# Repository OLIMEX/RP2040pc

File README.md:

# RP2040pc
All in one computer with 4 USB hosts, Stereo Audio, HDMI output. Supports USB Flash drives, USB keyboards, USB Gamepads.

https://www.olimex.com/Products/RaspberryPi/RP2040pc/

## Licensee
* Hardware is released under CERN Open Hardware Licence Version 2 - Strongly Reciprocal
* Software is released under MIT Licensee
* Documentation is released under CC BY-SA 4.0

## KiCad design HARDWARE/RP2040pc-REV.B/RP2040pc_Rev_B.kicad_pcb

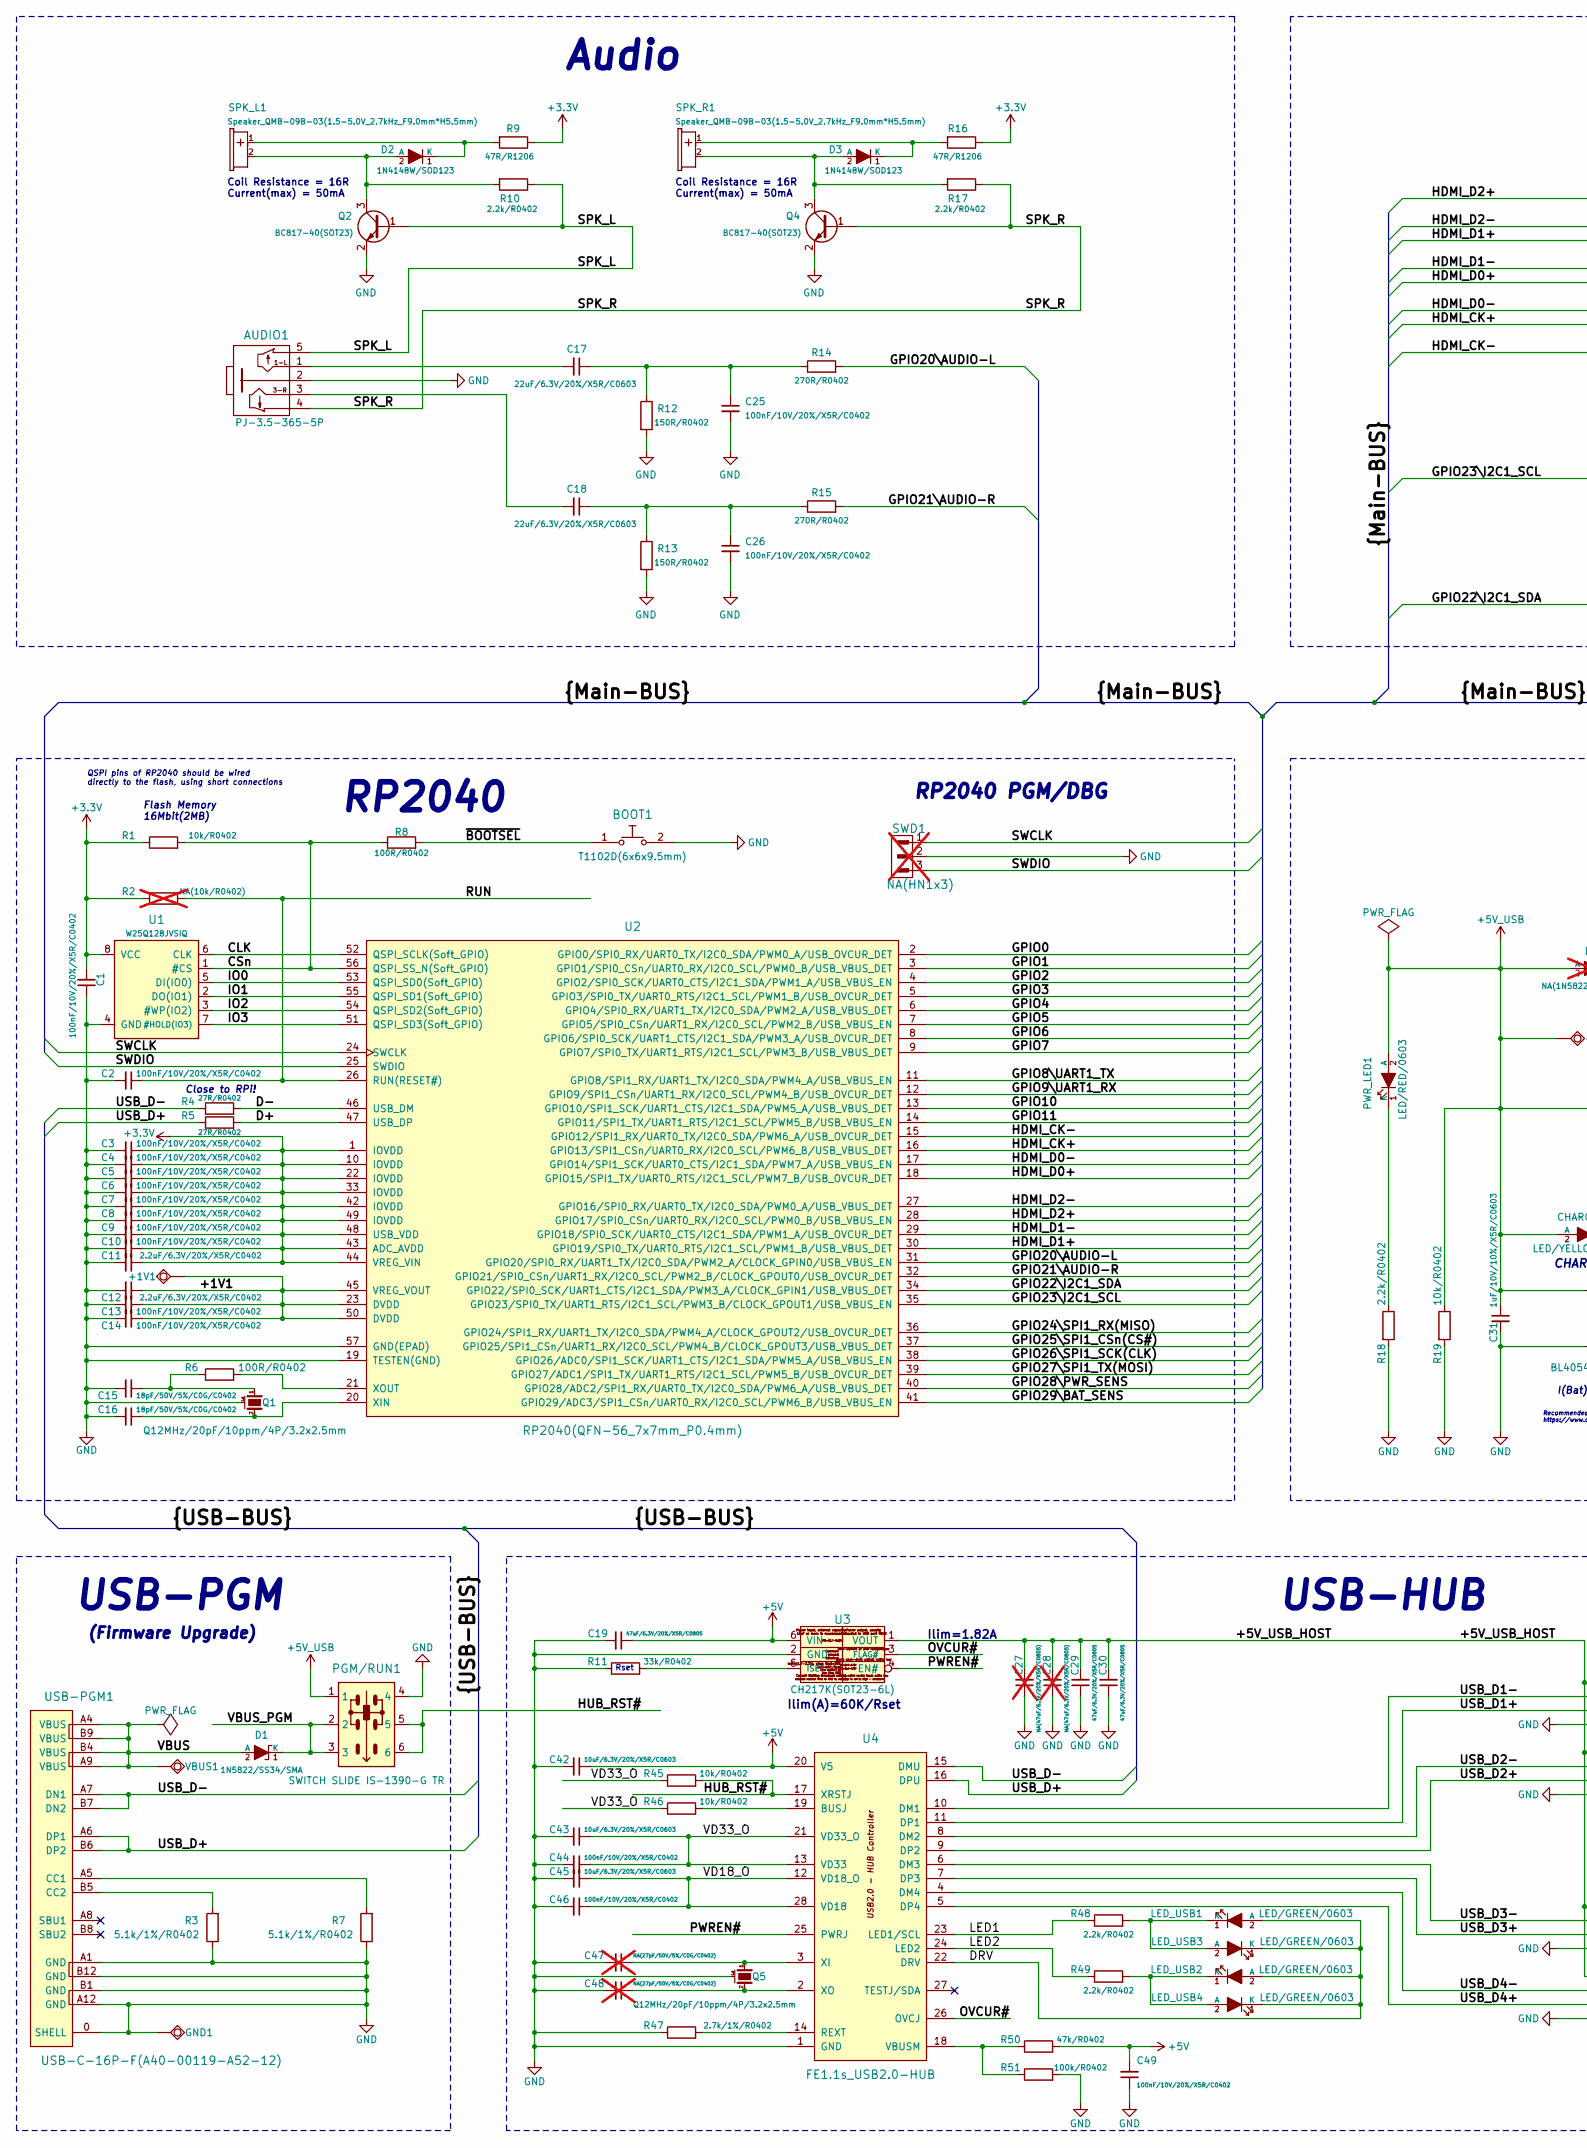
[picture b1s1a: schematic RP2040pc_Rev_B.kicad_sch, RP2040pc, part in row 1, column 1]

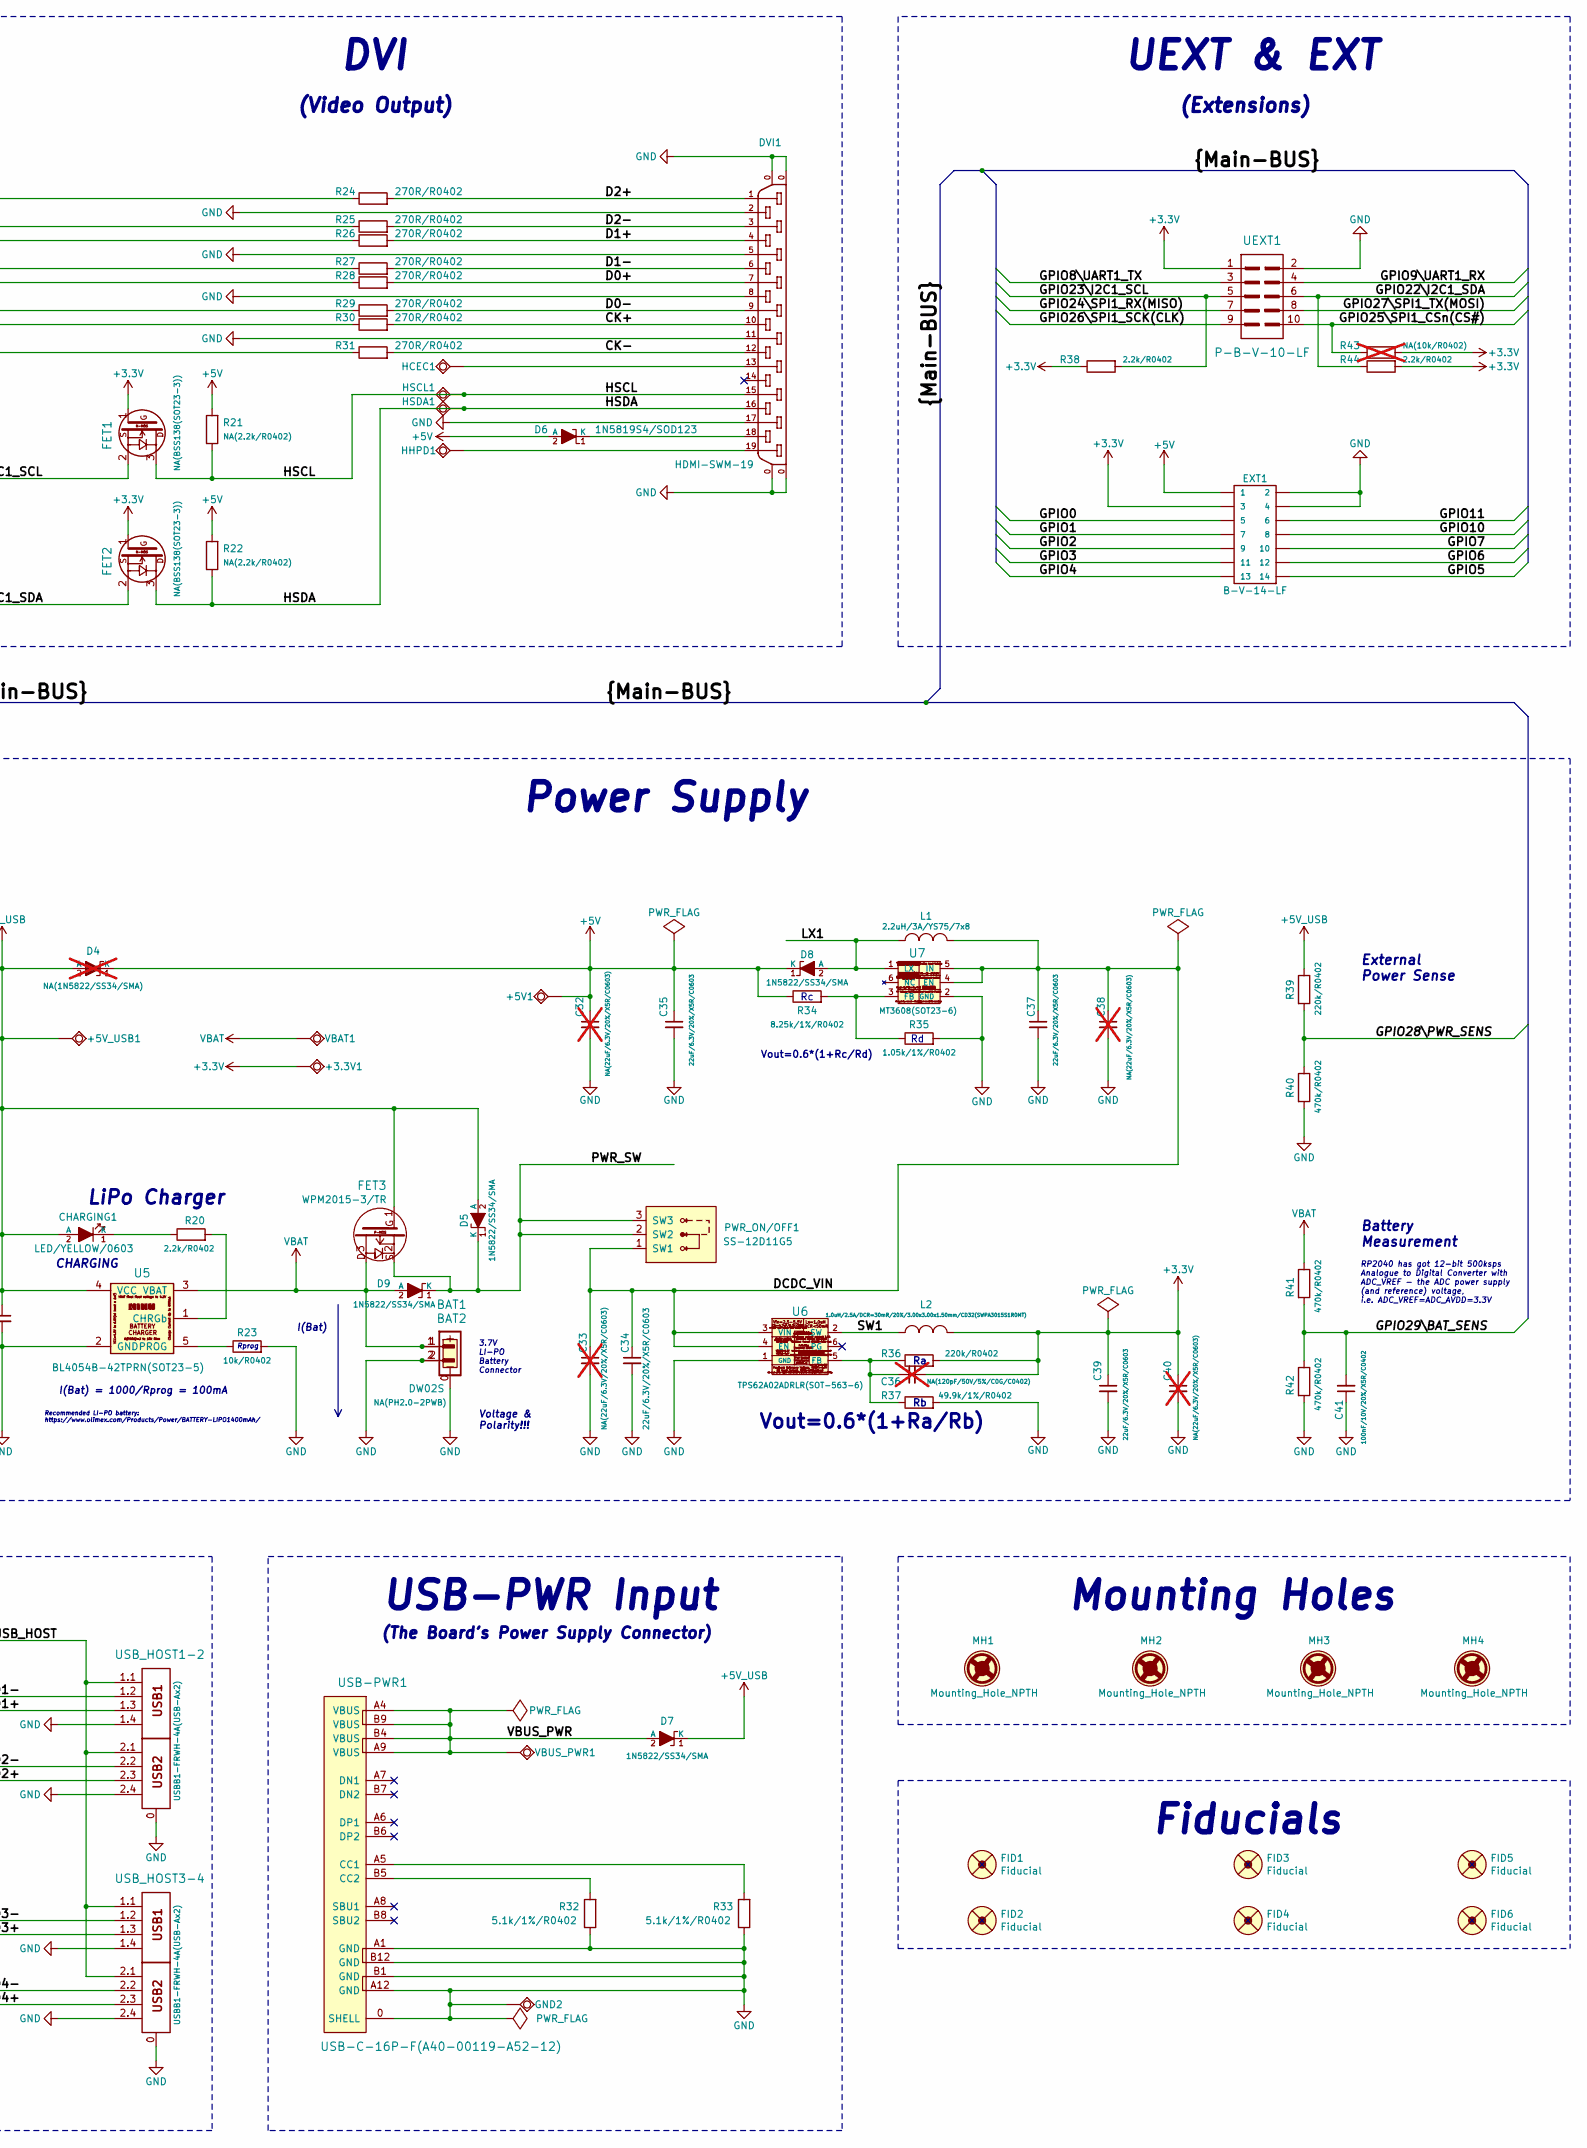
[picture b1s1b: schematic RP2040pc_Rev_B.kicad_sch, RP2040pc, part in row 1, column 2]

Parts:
+1V1, +3.3V1, +5V1, +5V_USB1: TESTPAD; TESTPAD_40-ROUND
AUDIO1: PJ-3.5-365-5P; SCJ325P00XG0B02G
BAT1: DW02S; LIPO_BAT_VERTICAL_DW02S
BAT2: NA(PH2.0-2PWB); PH2.0-2PWB
BOOT1: T1102D(6x6x9.5mm); T1102D_6x6
C1, C2, C3, C4, C5, C6, C7, C8, C9, C10, C13, C14, C25, C26, C41, C44, C46, C49: 100nF/10V/20%/X5R/C0402; C_0402_5MIL_DWS
C11, C12: 2.2uF/6.3V/20%/X5R/C0402; C_0402_5MIL_DWS
C15, C16: 18pF/50V/5%/C0G/C0402; C_0402_5MIL_DWS
C17, C18, C34, C35, C37, C39: 22uF/6.3V/20%/X5R/C0603; C_0603_5MIL_DWS
C19, C29, C30: 47uF/6.3V/20%/X5R/C0805; C_0805_5MIL_DWS
C27, C28: NA(47uF/6.3V/20%/X5R/C0805); C_0805_5MIL_DWS; not fitted
C31: 1uF/10V/10%/X5R/C0603; C_0603_5MIL_DWS
C32, C33, C38, C40: NA(22uF/6.3V/20%/X5R/C0603); C_0603_5MIL_DWS; not fitted
C36: NA(120pF/50V/5%/C0G/C0402); C_0402_5MIL_DWS; not fitted
C42, C43, C45: 10uF/6.3V/20%/X5R/C0603; C_0603_5MIL_DWS
C47, C48: NA(27pF/50V/5%/C0G/C0402); C_0402_5MIL_DWS; not fitted
CHARGING1: LED/YELLOW/0603; LED_0603_KA
D1, D5, D7, D8, D9: 1N5822/SS34/SMA; SMA-KA
D2, D3: 1N4148W/SOD123; SOD-123_1C-2A_KA
D4: NA(1N5822/SS34/SMA); SMA-KA; not fitted
D6: 1N5819S4/SOD123; SOD-123_1C-2A_KA
DVI1: HDMI-SWM-19; HDMI-SWM-19_Paste
EXT1: B-V-14-LF; GBH-254-SMT-14
FET1, FET2: NA(BSS138(SOT23-3)); SOT23
FET3: WPM2015-3/TR; SOT23
FID1, FID2, FID3: Fiducial; Fiducial1x3_Paste
FID4, FID5, FID6: Fiducial; Fiducial1x3
GND1: TESTPAD; TEST_PAD40x70_SQUARE
GND2: TESTPAD; TESTPAD_40-ROUND
HCEC1: TESTPAD; TESTPAD_40-ROUND
HHPD1: TESTPAD; TESTPAD_40-ROUND
HSCL1: TESTPAD; TESTPAD_40-ROUND
HSDA1: TESTPAD; TESTPAD_40-ROUND
L1: 2.2uH/3A/YS75/7x8; YS75_7X8MM
L2: 1.0uH/2.5A/DCR=30mR/20%/3.00x3.00x1.50mm/CD32(SWP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; CD32
LED_USB1, LED_USB2, LED_USB3, LED_USB4: LED/GREEN/0603; LED_0603_KA
MH1, MH2, MH3, MH4: Mounting_Hole_NPTH; Mounting_Hole_Drill-3.3mm_Clerance-7mm
PGM/RUN1: SWITCH SLIDE IS-1390-G TR; SWITCH_SLIDE_IS-1390-G_TR
PWR_LED1: LED/RED/0603; LED_0603_KA
PWR_ON/OFF1: SS-12D11G5
Q1, Q5: Q12MHz/20pF/10ppm/4P/3.2x2.5mm; TSX-3.2x2.5mm_GND(3)
Q2, Q4: BC817-40(SOT23); SOT23
R1, R19, R23, R45, R46: 10k/R0402; R_0402_5MIL_DWS
R2, R43: NA(10k/R0402); R_0402_5MIL_DWS; not fitted
R3, R7, R32, R33: 5.1k/1%/R0402; R_0402_5MIL_DWS
R4, R5: 27R/R0402; R_0402_5MIL_DWS
R6, R8: 100R/R0402; R_0402_5MIL_DWS
R9, R16: 47R/R1206; R_1206_5MIL_DWS
R10, R17, R18, R20, R38, R44, R48, R49: 2.2k/R0402; R_0402_5MIL_DWS
R11: 33k/R0402; R_0402_5MIL_DWS
R12, R13: 150R/R0402; R_0402_5MIL_DWS
R14, R15, R24, R25, R26, R27, R28, R29, R30, R31: 270R/R0402; R_0402_5MIL_DWS
R21, R22: NA(2.2k/R0402); R_0402_5MIL_DWS
R34: 8.25k/1%/R0402; R_0402_5MIL_DWS
R35: 1.05k/1%/R0402; R_0402_5MIL_DWS
R36, R39: 220k/R0402; R_0402_5MIL_DWS
R37: 49.9k/1%/R0402; R_0402_5MIL_DWS
R40, R41, R42: 470k/R0402; R_0402_5MIL_DWS
R47: 2.7k/1%/R0402; R_0402_5MIL_DWS
R50: 47k/R0402; R_0402_5MIL_DWS
R51: 100k/R0402; R_0402_5MIL_DWS
SPK_L1: Speaker_QMB-09B-03(1.5-5.0V_2.7kHz_F9.0mm*H5.5mm); Speaker_QMB-09B-03_1-Plus_2-Minus
SPK_R1: Speaker_QMB-09B-03(1.5-5.0V_2.7kHz_F9.0mm*H5.5mm); Speaker_QMB-09B-03_1-Plus_2-Minus
SWD1: NA(HN1x3); HN1x3; not fitted
U1: W25Q128JVSIQ; SO-8_208mil
U2: RP2040(QFN-56_7x7mm_P0.4mm); QFN56_7x7_Pitch_0.4mm
U3: CH217K(SOT23-6L); SOT23-6
U4: FE1.1s_USB2.0-HUB; SSOP28_10x4mm_Pitch_0.64mm
U5: BL4054B-42TPRN(SOT23-5); SOT-23-5
U6: TPS62A02ADRLR(SOT-563-6); SOT-563-6
U7: MT3608(SOT23-6); SOT23-6
UEXT1: P-B-V-10-LF; GBH-254-SMT-10
USB-PGM1: USB-C-16P-F(A40-00119-A52-12); USB2.0_TYPE-C(A40-00119-A52-12)_Paste
USB-PWR1: USB-C-16P-F(A40-00119-A52-12); USB2.0_TYPE-C(A40-00119-A52-12)_Paste
USB_HOST1-2, USB_HOST3-4: USBB1-FRWH-4A(USB-Ax2); USB_TWO_LEVEL
VBAT1: TESTPAD; TESTPAD_40-ROUND
VBUS1: TESTPAD; TESTPAD_40-ROUND
VBUS_PWR1: TESTPAD; TESTPAD_40-ROUND

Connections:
+3.3V: +3.3V1.1 (Pad), C1.2, C3.1, C4.1, C5.1, C6.1, C7.1, C8.1, C9.1, C10.1, C11.1, C36.2, C39.1, C40.1, EXT1.3, FET1.1 (G), FET2.1 (G), L2.2, R1.1, R2.1, R9.1, R16.1, R36.2, R38.1, R43.2, R44.2, U1.8 (VCC), U2.1 (IOVDD), U2.10 (IOVDD), U2.22 (IOVDD), U2.33 (IOVDD), U2.42 (IOVDD), U2.43 (ADC_AVDD), U2.44 (VREG_VIN), U2.48 (USB_VDD), U2.49 (IOVDD), UEXT1.1
+5V: +5V1.1 (Pad), C19.1, C32.1, C35.1, C42.1, C49.2, D4.1 (K), D6.2 (A), D8.1 (K), EXT1.1, R21.2, R22.2, R34.1, R50.2, U3.6 (VIN), U4.20 (V5)
+5V_USB: +5V_USB1.1 (Pad), C31.1, CHARGING1.2 (A), D4.2 (A), D5.2 (A), D7.1 (K), FET3.1, PGM/RUN1.1, PWR_LED1.2 (A), R19.1, R39.1, U5.4 (VCC)
/+1V1: +1V1.1 (Pad), C12.1, C13.1, C14.1, U2.23 (DVDD), U2.45 (VREG_VOUT), U2.50 (DVDD)
/+5V_USB_HOST: C27.2, C28.2, C29.2, C30.2, U3.1 (VOUT), USB_HOST1-2.1.1, USB_HOST1-2.2.1, USB_HOST3-4.1.1, USB_HOST3-4.2.1
/CK+: DVI1.10, R30.2
/CK-: DVI1.12, R31.2
/CLK: U1.6 (CLK), U2.52 (QSPI_SCLK(Soft_GPIO))
/CSn: R1.2, R8.1, U1.1 (#CS), U2.56 (QSPI_SS_N(Soft_GPIO))
/D0+: DVI1.7, R28.2
/D0-: DVI1.9, R29.2
/D1+: DVI1.4, R26.2
/D1-: DVI1.6, R27.2
/D2+: DVI1.1, R24.2
/D2-: DVI1.3, R25.2
/D+: R5.2, U2.47 (USB_DP)
/D-: R4.2, U2.46 (USB_DM)
/DCDC_VIN: C33.1, C34.1, C37.1, C38.1, L1.2, PWR_ON/OFF1.1 (SW1), U6.3 (VIN), U6.4 (EN), U7.4 (EN), U7.5 (IN)
/DRV: LED_USB1.2 (A), LED_USB2.2 (A), LED_USB3.1 (K), LED_USB4.1 (K), U4.22 (DRV)
/GPIO0: EXT1.5, U2.2 (GPIO0/SPI0_RX/UART0_TX/I2C0_SDA/PWM0_A/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)
/GPIO1: EXT1.7, U2.3 (GPIO1/SPI0_CSn/UART0_RX/I2C0_SCL/PWM0_B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)
/GPIO2: EXT1.9, U2.4 (GPIO2/SPI0_SCK/UART0_CTS/I2C1_SDA/PWM1_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)
/GPIO3: EXT1.11, U2.5 (GPIO3/SPI0_TX/UART0_RTS/I2C1_SCL/PWM1_B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)
/GPIO4: EXT1.13, U2.6 (GPIO4/SPI0_RX/UART1_TX/I2C0_SDA/PWM2_A/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)
/GPIO5: EXT1.14, U2.7 (GPIO5/SPI0_CSn/UART1_RX/I2C0_SCL/PWM2_B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)
/GPIO6: EXT1.12, U2.8 (GPIO6/SPI0_SCK/UART1_CTS/I2C1_SDA/PWM3_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)
/GPIO7: EXT1.10, U2.9 (GPIO7/SPI0_TX/UART1_RTS/I2C1_SCL/PWM3_B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)
/GPIO8\UART1_TX: U2.11 (GPIO8/SPI1_RX/UART1_TX/I2C0_SDA/PWM4_A/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), UEXT1.3
/GPIO9\UART1_RX: U2.12 (GPIO9/SPI1_CSn/UART1_RX/I2C0_SCL/PWM4_B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), UEXT1.4
/GPIO10: EXT1.8, U2.13 (GPIO10/SPI1_SCK/UART1_CTS/I2C1_SDA/PWM5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)
/GPIO11: EXT1.6, U2.14 (GPIO11/SPI1_TX/UART1_RTS/I2C1_SCL/PWM5_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)
/GPIO20\AUDIO-L: R14.2, U2.31 (GPIO20/SPI0_RX/UART1_TX/I2C0_SDA/PWM2_A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)
/GPIO21\AUDIO-R: R15.2, U2.32 (GPIO21/SPI0_CSn/UART1_RX/I2C0_SCL/PWM2_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)
/GPIO22\I2C1_SDA: FET2.2 (S), R44.1, U2.34 (GPIO22/SPI0_SCK/UART1_CTS/I2C1_SDA/PWM3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), UEXT1.6
/GPIO23\I2C1_SCL: FET1.2 (S), R38.2, U2.35 (GPIO23/SPI0_TX/UART1_RTS/I2C1_SCL/PWM3_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), UEXT1.5
/GPIO24\SPI1_RX(MISO): U2.36 (GPIO24/SPI1_RX/UART1_TX/I2C0_SDA/PWM4_A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), UEXT1.7
/GPIO25\SPI1_CSn(CS#): R43.1, U2.37 (GPIO25/SPI1_CSn/UART1_RX/I2C0_SCL/PWM4_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), UEXT1.10
/GPIO26\SPI1_SCK(CLK): U2.38 (GPIO26/ADC0/SPI1_SCK/UART1_CTS/I2C1_SDA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), UEXT1.9
/GPIO27\SPI1_TX(MOSI): U2.39 (GPIO27/ADC1/SPI1_TX/UART1_RTS/I2C1_SCL/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), UEXT1.8
/GPIO28\PWR_SENS: R39.2, R40.1, U2.40 (GPIO28/ADC2/SPI1_RX/UART0_TX/I2C0_SDA/P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)
/GPIO29\BAT_SENS: C41.2, R41.2, R42.1, U2.41 (GPIO29/ADC3/SPI1_CSn/UART0_RX/I2C0_SCL/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)
/HDMI_CK+: R30.1, U2.16 (GPIO13/SPI1_CSn/UART0_RX/I2C0_SCL/PWM6_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)
/HDMI_CK-: R31.1, U2.15 (GPIO12/SPI1_RX/UART0_TX/I2C0_SDA/PWM6_A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)
/HDMI_D0+: R28.1, U2.18 (GPIO15/SPI1_TX/UART0_RTS/I2C1_SCL/PWM7_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)
/HDMI_D0-: R29.1, U2.17 (GPIO14/SPI1_SCK/UART0_CTS/I2C1_SDA/PWM7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)
/HDMI_D1+: R26.1, U2.30 (GPIO19/SPI0_TX/UART0_RTS/I2C1_SCL/PWM1_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)
/HDMI_D1-: R27.1, U2.29 (GPIO18/SPI0_SCK/UART0_CTS/I2C1_SDA/PWM1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)
/HDMI_D2+: R24.1, U2.28 (GPIO17/SPI0_CSn/UART0_RX/I2C0_SCL/PWM0_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)
/HDMI_D2-: R25.1, U2.27 (GPIO16/SPI0_RX/UART0_TX/I2C0_SDA/PWM0_A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)
/HSCL: DVI1.15, FET1.3 (D), HSCL1.1 (Pad), R21.1
/HSDA: DVI1.16, FET2.3 (D), HSDA1.1 (Pad), R22.1
/HUB_RST#: PGM/RUN1.5, PGM/RUN1.6, R45.2, U4.17 (XRSTJ)
/IO0: U1.5 (DI(IO0)), U2.53 (QSPI_SD0(Soft_GPIO))
/IO1: U1.2 (DO(IO1)), U2.55 (QSPI_SD1(Soft_GPIO))
/IO2: U1.3 (#WP(IO2)), U2.54 (QSPI_SD2(Soft_GPIO))
/IO3: U1.7 (#HOLD(IO3)), U2.51 (QSPI_SD3(Soft_GPIO))
/LED1: R48.1, U4.23 (LED1/SCL)
/LED2: R49.1, U4.24 (LED2)
/LX1: D8.2 (A), L1.1, U7.1 (LX)
/OVCUR#: U3.3 (FLAG#), U4.26 (OVCJ)
/PWREN#: U3.4 (EN#), U4.25 (PWRJ)
/PWR_SW: D5.1 (K), D9.1 (K), FET3.2, PWR_ON/OFF1.2 (SW2), PWR_ON/OFF1.3 (SW3)
/RUN: C2.1, R2.2, U2.26 (RUN(RESET#))
/SPK_L: AUDIO1.5, Q2.1 (B), R10.1
/SPK_R: AUDIO1.4, Q4.1 (B), R17.1
/SW1: L2.1, U6.2 (SW)
/SWCLK: SWD1.1, U2.24 (SWCLK)
/SWDIO: SWD1.3, U2.25 (SWDIO)
/USB_D1+: U4.11 (DP1), USB_HOST1-2.1.3
/USB_D1-: U4.10 (DM1), USB_HOST1-2.1.2
/USB_D2+: U4.9 (DP2), USB_HOST1-2.2.3
/USB_D2-: U4.8 (DM2), USB_HOST1-2.2.2
/USB_D3+: U4.7 (DP3), USB_HOST3-4.1.3
/USB_D3-: U4.6 (DM3), USB_HOST3-4.1.2
/USB_D4+: U4.5 (DP4), USB_HOST3-4.2.3
/USB_D4-: U4.4 (DM4), USB_HOST3-4.2.2
/USB_D+: R5.1, U4.16 (DPU), USB-PGM1.A6 (DP1), USB-PGM1.B6 (DP2)
/USB_D-: R4.1, U4.15 (DMU), USB-PGM1.A7 (DN1), USB-PGM1.B7 (DN2)
/VBUS: D1.2 (A), USB-PGM1.A4 (VBUS), USB-PGM1.A9 (VBUS), USB-PGM1.B4 (VBUS), USB-PGM1.B9 (VBUS), VBUS1.1 (Pad)
/VBUS_PGM: D1.1 (K), PGM/RUN1.2, PGM/RUN1.3
/VBUS_PWR: D7.2 (A), USB-PWR1.A4 (VBUS), USB-PWR1.A9 (VBUS), USB-PWR1.B4 (VBUS), USB-PWR1.B9 (VBUS), VBUS_PWR1.1 (Pad)
/VD18_O: C45.1, C46.1, U4.12 (VD18_O), U4.28 (VD18)
/VD33_O: C43.1, C44.1, R45.1, R46.1, U4.13 (VD33), U4.21 (VD33_O)
/~BOOTSEL: BOOT1.1, R8.2
GND: AUDIO1.2, BAT1.2, BAT2.0, BAT2.2, BOOT1.2, C1.1, C2.2, C3.2, C4.2, C5.2, C6.2, C7.2, C8.2, C9.2, C10.2, C11.2, C12.2, C13.2, C14.2, C15.2, C16.2, C19.2, C25.2, C26.2, C27.1, C28.1, C29.1, C30.1, C31.2, C32.2, C33.2, C34.2, C35.2, C37.2, C38.2, C39.2, C40.2, C41.1, C42.2, C43.2, C44.2, C45.2, C46.2, C47.2, C48.2, C49.1, DVI1.0 (22), DVI1.2, DVI1.5, DVI1.8, DVI1.11, DVI1.17, EXT1.2, EXT1.4, GND1.1 (Pad), GND2.1 (Pad), PGM/RUN1.4, Q1.3 (case), Q2.2 (E), Q4.2 (E), Q5.3 (case), R3.1, R7.1, R11.1, R12.2, R13.2, R18.2, R19.2, R23.2, R32.1, R33.1, R35.2, R37.2, R40.2, R42.2, R47.1, R51.2, SWD1.2, U1.4 (GND), U2.19 (TESTEN(GND)), U2.57 (GND(EPAD)), U3.2 (GND), U4.1 (GND), U5.2 (GND), U6.1 (GND), U7.2 (GND), UEXT1.2, USB-PGM1.0 (SHELL), USB-PGM1.A1 (GND), USB-PGM1.A12 (GND), USB-PGM1.B1 (GND), USB-PGM1.B12 (GND), USB-PWR1.0 (SHELL), USB-PWR1.A1 (GND), USB-PWR1.A12 (GND), USB-PWR1.B1 (GND), USB-PWR1.B12 (GND), USB_HOST1-2.0, USB_HOST1-2.1.4, USB_HOST1-2.2.4, USB_HOST3-4.0, USB_HOST3-4.1.4, USB_HOST3-4.2.4
unnamed: AUDIO1.1, C17.2
unnamed: AUDIO1.3, C18.2
unnamed: C15.1, Q1.1, R6.1
unnamed: C17.1, C25.1, R12.1, R14.1
unnamed: C18.1, C26.1, R13.1, R15.1
unnamed: CHARGING1.1 (K), R20.1
unnamed: D2.2 (A), Q2.3 (C), R10.2, SPK_L1.2 (MINUS)
unnamed: D2.1 (K), R9.2, SPK_L1.1 (PLUS)
unnamed: D3.2 (A), Q4.3 (C), R17.2, SPK_R1.2 (MINUS)
unnamed: D3.1 (K), R16.2, SPK_R1.1 (PLUS)
unnamed: D6.1 (K), DVI1.18
unnamed: DVI1.13, HCEC1.1 (Pad)
unnamed: DVI1.19, HHPD1.1 (Pad)
unnamed: LED_USB1.1 (K), LED_USB3.2 (A), R48.2
unnamed: LED_USB2.1 (K), LED_USB4.2 (A), R49.2
unnamed: PWR_LED1.1 (K), R18.1
unnamed: C16.1, Q1.2, U2.20 (XIN)
unnamed: R6.2, U2.21 (XOUT)
unnamed: R11.2, U3.5 (ISET)
unnamed: R46.2, U4.19 (BUSJ)
unnamed: R47.2, U4.14 (REXT)
unnamed: R50.1, R51.1, U4.18 (VBUSM)
unnamed: C47.1, Q5.1, U4.3 (XI)
unnamed: C48.1, Q5.2, U4.2 (XO)
unnamed: R20.2, U5.1 (CHRGb)
unnamed: R23.1, U5.5 (PROG)
unnamed: C36.1, R36.1, R37.1, U6.5 (FB)
unnamed: R34.2, R35.1, U7.3 (FB)
unnamed: R7.2, USB-PGM1.A5 (CC1)
unnamed: R3.2, USB-PGM1.B5 (CC2)
unnamed: R33.2, USB-PWR1.A5 (CC1)
unnamed: R32.2, USB-PWR1.B5 (CC2)
VBAT: BAT1.1, BAT2.1, D9.2 (A), FET3.3, R41.1, U5.3 (VBAT), VBAT1.1 (Pad)

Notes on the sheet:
Battery Measurement
(Firmware Upgrade)
Vout=0.6*(1+Ra/Rb)
Ilim(A)=60K/Rset
QSPI pins of RP2040 should be wired directly to the flash, using short connections
RP2040 has got 12-bit 500ksps Analogue to Digital Converter with ADC_VREF - the ADC power supply (and reference) voltage, i.e. ADC_VREF=ADC_AVDD=3.3V
Recommended LI-PO battery: https://www.olimex.com/Products/Power/BATTERY-LIPO1400mAh/
(Video Output)
(Extensions)
3.7V LI-PO Battery Connector
USB-PGM
USB-HUB
Close to RPi!
Vout=0.6*(1+Rc/Rd)
Coil Resistance = 16R Current(max) = 50mA
I(Bat)
LiPo Charger
UEXT & EXT
(The Board's Power Supply Connector)
I(Bat) = 1000/Rprog = 100mA
Mounting Holes
CHARGING
Fiducials
Audio
Power Supply
Ilim=1.82A
RP2040 PGM/DBG
DVI
RP2040
USB-PWR Input
Voltage & Polarity!!!
External Power Sense
Flash Memory 16Mbit(2MB)
Rset
Rprog

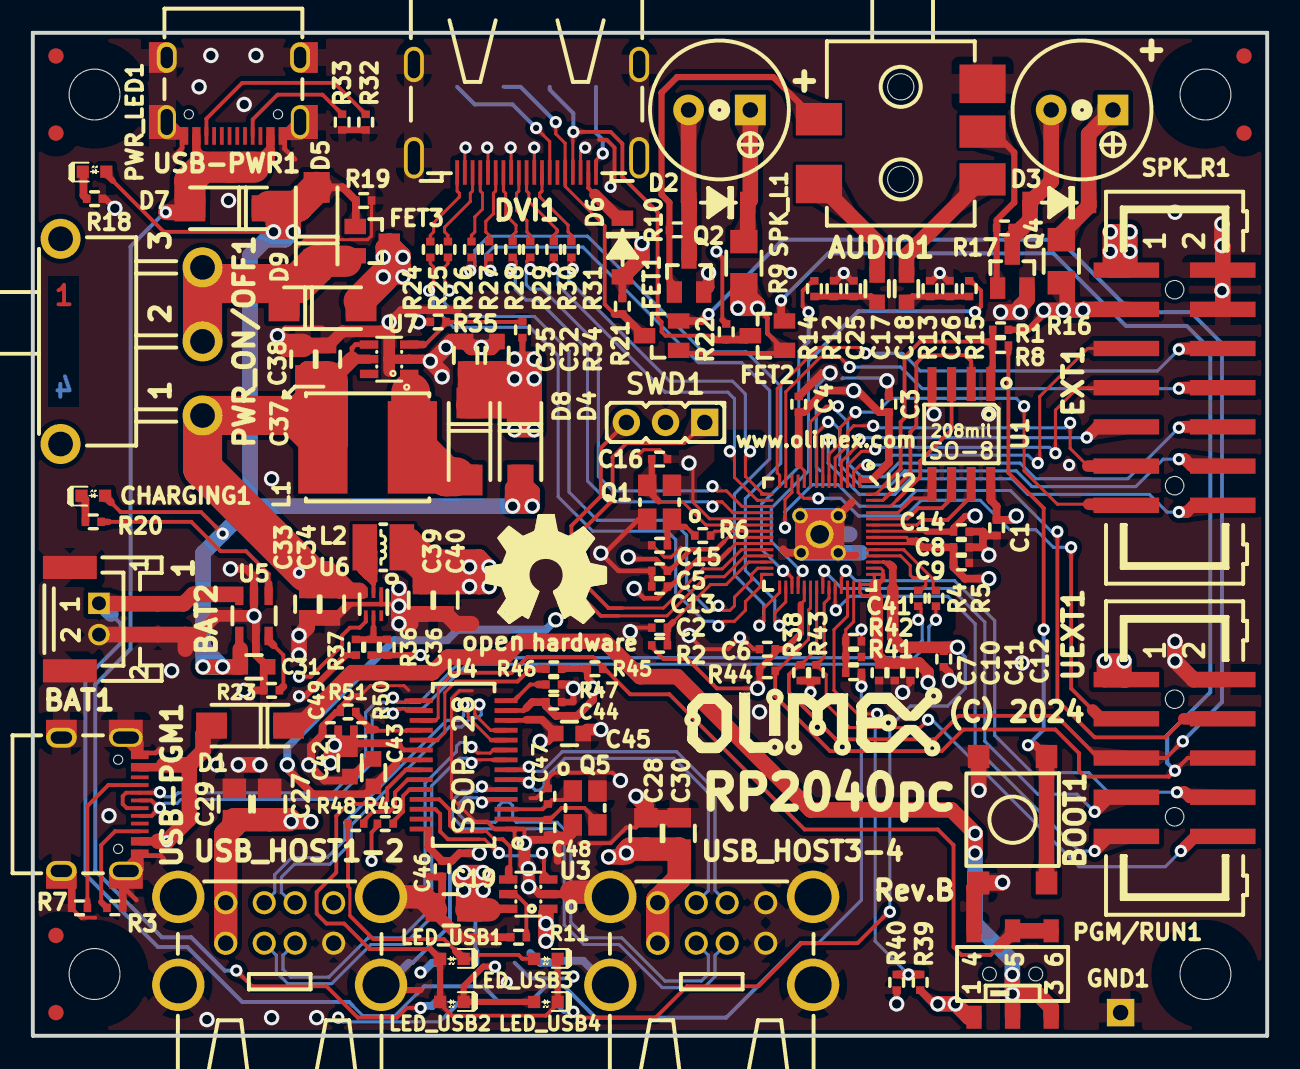
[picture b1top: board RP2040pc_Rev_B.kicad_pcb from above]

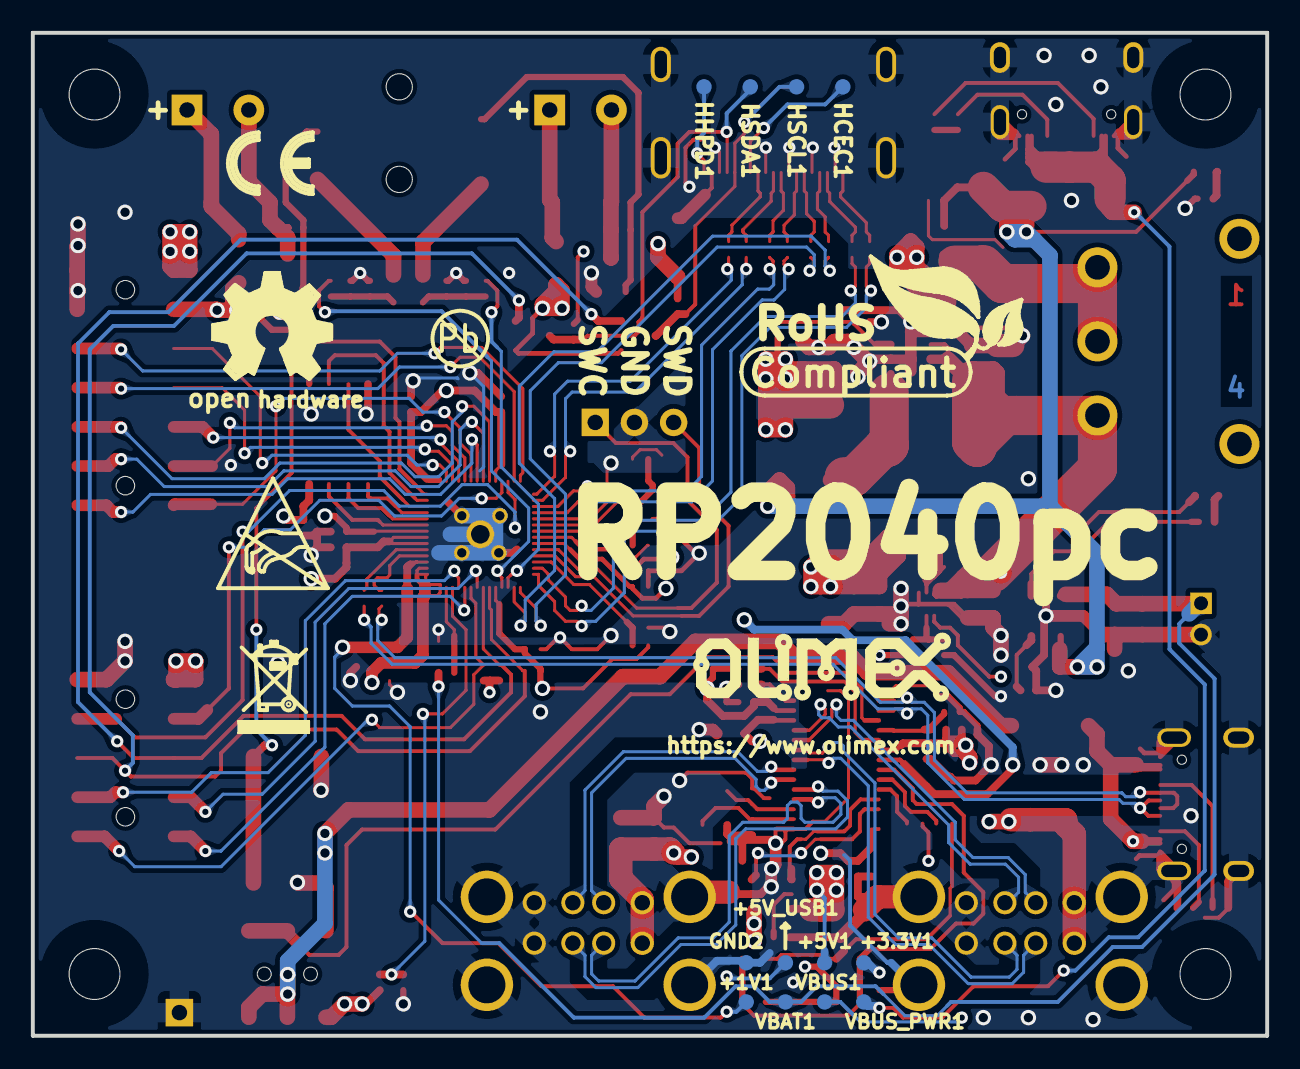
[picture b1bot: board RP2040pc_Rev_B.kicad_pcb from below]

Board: 4 copper layers, 80.0 x 65.0 mm, 174 parts (19 on the bottom side), 118 nets.

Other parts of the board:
Logo_OLIMEX_TB: Logo_OLIMEX_TB
Logo_OLIMEX_TB-Top: Logo_OLIMEX_TB
Sign_Antistatic: Sign_Antistatic
Sign_CE: CE_Sign
Sign_OSHW_8x8, Sign_OSHW_8x8-Top: Sign_OSHW_8x8
Sign_PB-Free: Sign_PB-Free
Sign_RecycleBin: Sign_RecycleBin; Sign_RecycleBin_1
Sign_RoHS: Sign_RoHS; Sign_RoHS_1

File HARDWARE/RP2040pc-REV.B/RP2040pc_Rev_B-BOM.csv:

"Id";"Designator";"Footprint";"Quantity";"Designation";"Supplier and ref";
1;"MH1,MH3,MH4,MH2";"Mounting_Hole_Drill-3.3mm_Clerance-7mm";4;"Mounting_Hole_NPTH";;;
2;"R38,R44,R10,R20,R17,R49,R48,R18";"R_0402_5MIL_DWS";8;"2.2k/R0402";;;
3;"R12,R13";"R_0402_5MIL_DWS";2;"150R/R0402";;;
4;"R14,R31,R28,R25,R24,R27,R26,R29,R30,R15";"R_0402_5MIL_DWS";10;"270R/R0402";;;
5;"FID5,FID6,FID4";"Fiducial1x3";3;"Fiducial";;;
6;"FID2,FID3,FID1";"Fiducial1x3_Paste";3;"Fiducial";;;
7;"C17,C34,C37,C18,C39,C35";"C_0603_5MIL_DWS";6;"22uF/6.3V/20%/X5R/C0603";;;
8;"C25,C1,C2,C3,C4,C5,C6,C7,C8,C9,C10,C14,C13,C44,C46,C26,C41,C49";"C_0402_5MIL_DWS";18;"100nF/10V/20%/X5R/C0402";;;
9;"AUDIO1";"SCJ325P00XG0B02G";1;"PJ-3.5-365-5P";;;
10;"Q2,Q4";"SOT23";2;"BC817-40(SOT23)";;;
11;"C11,C12";"C_0402_5MIL_DWS";2;"2.2uF/6.3V/20%/X5R/C0402";;;
12;"C15,C16";"C_0402_5MIL_DWS";2;"18pF/50V/5%/C0G/C0402";;;
13;"Q1,Q5";"TSX-3.2x2.5mm_GND(3)";2;"Q12MHz/20pF/10ppm/4P/3.2x2.5mm";;;
14;"R1,R45,R23,R46,R19";"R_0402_5MIL_DWS";5;"10k/R0402";;;
15;"R2,R43";"R_0402_5MIL_DWS";2;"NA(10k/R0402)";;;
16;"R6,R8";"R_0402_5MIL_DWS";2;"100R/R0402";;;
17;"R4,R5";"R_0402_5MIL_DWS";2;"27R/R0402";;;
18;"U1";"SO-8_208mil";1;"W25Q128JVSIQ ";;;
19;"U2";"QFN56_7x7_Pitch_0.4mm";1;"RP2040(QFN-56_7x7mm_P0.4mm)";;;
20;"BOOT1";"T1102D_6x6";1;"T1102D(6x6x9.5mm)";;;
21;"SWD1";"HN1x3";1;"NA(HN1x3)";;;
22;"R9,R16";"R_1206_5MIL_DWS";2;"47R/R1206";;;
23;"DVI1";"HDMI-SWM-19_Paste";1;"HDMI-SWM-19";;;
24;"SPK_L1,SPK_R1";"Speaker_QMB-09B-03_1-Plus_2-Minus";2;"Speaker_QMB-09B-03(1.5-5.0V_2.7kHz_F9.0mm*H5.5mm)";;;
25;"D2,D3";"SOD-123_1C-2A_KA";2;"1N4148W/SOD123";;;
26;"C40,C38,C32,C33";"C_0603_5MIL_DWS";4;"NA(22uF/6.3V/20%/X5R/C0603)";;;
27;"R35";"R_0402_5MIL_DWS";1;"1.05k/1%/R0402";;;
28;"USB_HOST1-2,USB_HOST3-4";"USB_TWO_LEVEL";2;"USBB1-FRWH-4A(USB-Ax2)";;;
29;"LED_USB4,LED_USB3,LED_USB1,LED_USB2";"LED_0603_KA";4;"LED/GREEN/0603";;;
30;"U6";"SOT-563-6";1;"TPS62A02ADRLR(SOT-563-6)";;;
31;"R40,R42,R41";"R_0402_5MIL_DWS";3;"470k/R0402";;;
32;"C27,C28";"C_0805_5MIL_DWS";2;"NA(47uF/6.3V/20%/X5R/C0805)";;;
33;"C29,C19,C30";"C_0805_5MIL_DWS";3;"47uF/6.3V/20%/X5R/C0805";;;
34;"R22,R21";"R_0402_5MIL_DWS";2;"NA(2.2k/R0402)";;;
35;"PWR_ON/OFF1";"SS-12D11G5";1;"SS-12D11G5";;;
36;"EXT1";"GBH-254-SMT-14";1;"B-V-14-LF";;;
37;"R33,R32,R7,R3";"R_0402_5MIL_DWS";4;"5.1k/1%/R0402";;;
38;"U5";"SOT-23-5";1;"BL4054B-42TPRN(SOT23-5)";;;
39;"CHARGING1";"LED_0603_KA";1;"LED/YELLOW/0603";;;
40;"D7,D8,D5,D1,D9";"SMA-KA";5;"1N5822/SS34/SMA";;;
41;"UEXT1";"GBH-254-SMT-10";1;"P-B-V-10-LF";;;
42;"GND1";"TEST_PAD40x70_SQUARE";1;"TESTPAD";;;
43;"C31";"C_0603_5MIL_DWS";1;"1uF/10V/10%/X5R/C0603";;;
44;"R50";"R_0402_5MIL_DWS";1;"47k/R0402";;;
45;"FET2,FET1";"SOT23";2;"NA(BSS138(SOT23-3))";;;
46;"U4";"SSOP28_10x4mm_Pitch_0.64mm";1;"FE1.1s_USB2.0-HUB";;;
47;"PGM/RUN1";"SWITCH_SLIDE_IS-1390-G_TR";1;"SWITCH SLIDE IS-1390-G TR";;;
48;"U7";"SOT23-6";1;"MT3608(SOT23-6)";;;
49;"C43,C45,C42";"C_0603_5MIL_DWS";3;"10uF/6.3V/20%/X5R/C0603";;;
50;"U3";"SOT23-6";1;"CH217K(SOT23-6L)";;;
51;"R51";"R_0402_5MIL_DWS";1;"100k/R0402";;;
52;"USB-PGM1,USB-PWR1";"USB2.0_TYPE-C(A40-00119-A52-12)_Paste";2;"USB-C-16P-F(A40-00119-A52-12)";;;
53;"FET3";"SOT23";1;"WPM2015-3/TR";;;
54;"R47";"R_0402_5MIL_DWS";1;"2.7k/1%/R0402";;;
55;"C47,C48";"C_0402_5MIL_DWS";2;"NA(27pF/50V/5%/C0G/C0402)";;;
56;"BAT1";"LIPO_BAT_VERTICAL_DW02S";1;"DW02S";;;
57;"R37";"R_0402_5MIL_DWS";1;"49.9k/1%/R0402";;;
58;"R36,R39";"R_0402_5MIL_DWS";2;"220k/R0402";;;
59;"D6";"SOD-123_1C-2A_KA";1;"1N5819S4/SOD123";;;
60;"C36";"C_0402_5MIL_DWS";1;"NA(120pF/50V/5%/C0G/C0402)";;;
61;"R11";"R_0402_5MIL_DWS";1;"33k/R0402";;;
62;"D4";"SMA-KA";1;"NA(1N5822/SS34/SMA)";;;
63;"R34";"R_0402_5MIL_DWS";1;"8.25k/1%/R0402";;;
64;"L1";"YS75_7X8MM";1;"2.2uH/3A/YS75/7x8";;;
65;"PWR_LED1";"LED_0603_KA";1;"LED/RED/0603";;;
66;"BAT2";"PH2.0-2PWB";1;"NA(PH2.0-2PWB)";;;
67;"L2";"CD32";1;"1.0uH/2.5A/DCR=30mR/20%/3.00x3.00x1.50mm/CD32(SWPA3015S1R0MT)";;;
68;"HCEC1,HSDA1,HSCL1,HHPD1,+5V_USB1,GND2,VBUS1,+5V1,+1V1,VBAT1,VBUS_PWR1,+3.3V1";"TESTPAD_40-ROUND";12;"TESTPAD";;;

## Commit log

2024-12-11 initial upload

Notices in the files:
HARDWARE/RP2040pc-REV.B/RP2040pc_Rev_B.kicad_pcb:
(C) 2024
